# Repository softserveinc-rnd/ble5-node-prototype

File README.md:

# BLE5 node for prototyping

## Hardware Design

The designed system is built around Nordic nRF52840 module that is used as a main
communication and processing unit. 
Nordic Semiconductor’s nRF52840 Bluetooth Low Energy (BLE) System-on-Chip
(SoC) — the high-end variant of Nordic’s nRF52 Series of high-performance
Bluetooth 5-certified SoCs — brings a production-ready, multiprotocol wireless
IoT solution to the market with the full Bluetooth 5 support and support for Bluetooth
mesh and Thread.

The SoC offers the capabilities and flexibility to support a broad range of networked,
connected products for wearables, gaming, VR/AR, as well as home and industrial IoT applications
thanks to a wide range of features and peripherals.

The high-end nRF52840 SoC, based on Nordic’s proven nRF52 Series architecture,
is the first single-chip solution to bring all of the benefits of Bluetooth 5 to the market.
The key advantages of Bluetooth 5 compared to the previous implementations of the BLE specification
include: 2× on-air raw data bandwidth (2 Mb/s); 4× range; 8× broadcasting ability with advertising
extensions that increase the advertising packet payload size to 251 bytes; and an improved channel
coexistence algorithm.

The nRF52840 SoC uses a 64-MHz, 32-bit Arm Cortex M4F processor, floating point, and DSP performance
to meet the demands of challenging wireless applications. The SoC can also operate from the power
supplies above 5 V, such as rechargeable battery power sources.

Other features include a new radio architecture with a +8-dBm on-chip PA, 1-MB flash and 256-kB RAM,
IEEE 802.15.4 (including Thread), ANT, Zigbee, and proprietary 2.4-GHz wireless technologies;
a full-speed USB 2.0 controller; and a host of peripherals including a quad-SPI interface.
In terms of security, the SoC incorporates an Arm CryptoCell-310 cryptographic accelerator.
Extensive crypto-ciphers and key generation and storage options are also available.

There is a set of sensors to measure ambient and usage conditions: 

1. Temperature, humidity for monitoring environment (HTS221).
2. Inertial Measurement Unit(IMU) Accelerometer, gyroscope for monitoring node position, movement and fall detection (LSM6DSM).
3. Pressure sensor for altitude monitoring(LPS22HBTR, also can be used for navigation purposes)  
4. Lighting intensity sensor (OPT3001).

These sensors use I2C bus for communication with Nordic MCU.

The 1.8V LDO is used to power the system from LiPo battery. All the components were selected to run from low voltage level.
There are 2 power switches on the board that are controlled by Nordic chip. These switches are used to power sensors and flash memory.
To minimize power consumption during the sleep mode they can be turned off.

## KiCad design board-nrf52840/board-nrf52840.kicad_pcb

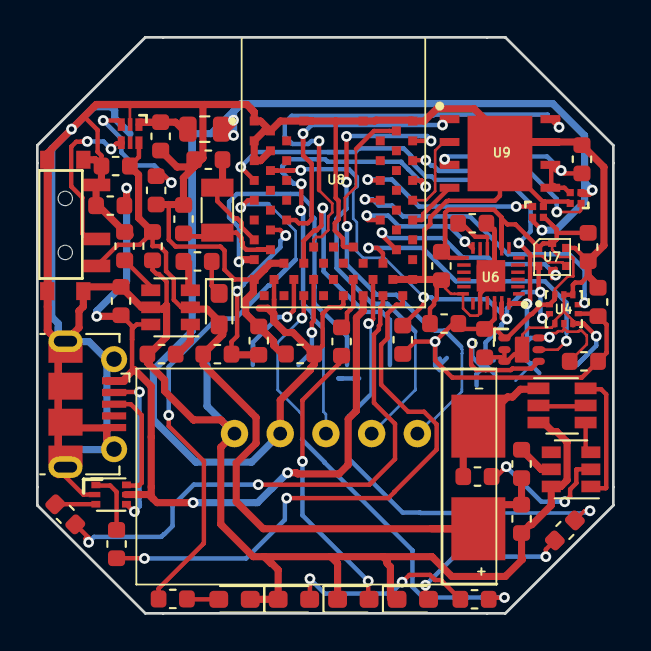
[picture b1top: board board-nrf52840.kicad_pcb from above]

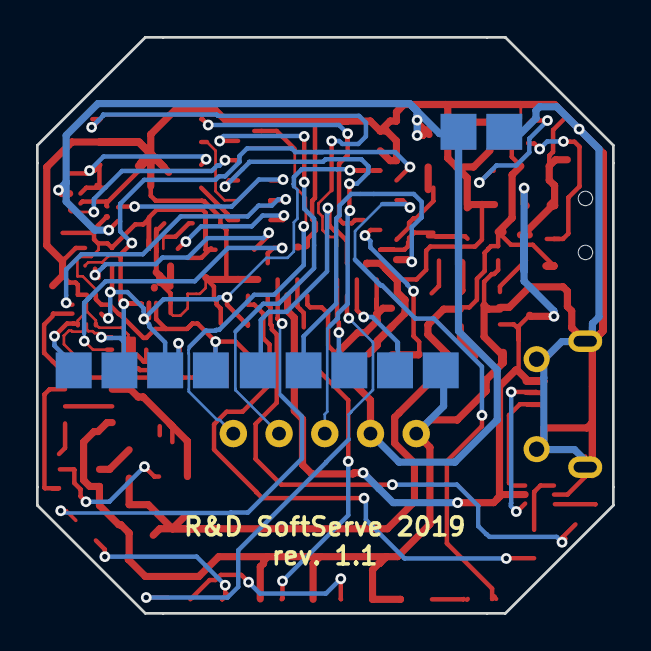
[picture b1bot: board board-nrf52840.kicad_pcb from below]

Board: 2 copper layers, 32.0 x 32.0 mm, 59 parts (4 on the bottom side), 56 nets.

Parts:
BT1: Battery; BATT-xx1220
C1, C3, C6: 1uF; C_0603_1608Metric
C2, C14: 0.1; C_0603_1608Metric
C4: 100nF; C_0603_1608Metric
C5, C9, C10, C11, C12, C17: 0.1uF; C_0603_1608Metric
C7: 4.7; C_0603_1608Metric
C8: 0.01; C_0603_1608Metric
C13: 4.7uF; C_0603_1608Metric
C15, C16: 6pF; C_0603_1608Metric
D1: LED; LED_0603_1608Metric_Pad1.05x0.95mm_HandSolder
D2: LED_RED; LED_0603_1608Metric_Pad1.05x0.95mm_HandSolder
D3: LED_GREEN; LED_0603_1608Metric_Pad1.05x0.95mm_HandSolder
D4: LED_BLUE; LED_0603_1608Metric_Pad1.05x0.95mm_HandSolder
D5: LED_YELLOW; LED_0603_1608Metric_Pad1.05x0.95mm_HandSolder
J1: USB_OTG; USB_Micro-B_Molex-105017-0001
J2: SWD
J3: Alternative_power; external_power
J4: Conn_01x05_Female; Pogo_5_pins
J5: I2C_sensors; 4x_pins
L1: 330 OHM @ 100MHz; L_0805_2012Metric
Q1: SMC8205AS; TSOT-23-6
R1, R4: 10k; R_0603_1608Metric
R2: 1.5k; R_0603_1608Metric
R3: 100R; R_0603_1608Metric
R5: 1k; R_0603_1608Metric
R6: 1M; R_0603_1608Metric
R7: 220k; R_0603_1608Metric
R8, R9: 4.7k; R_0603_1608Metric
R10, R11, R12, R13: 220R; R_0603_1608Metric
R14, R15: 27R; R_0603_1608Metric
SW1: SW_SPDT_GND; PCM12SMTR
U1: bq21040; SOT-23-6
U2: DW01; SOT-23-6
U3: USBLC6-2P6; SOT-666
U4: LPS22HBTR; LGA10R50P2X3_200X200X80
U6: Val**; ICM-20948
U7: HTS221; HLGA-6L
U8: BMD-340-A-R; BMD340AR
U9: AT45DB641E-MHN-Y; SON127P600X500X60-9N-D
U10, U12: SiP32475; μDFN-4L_1_mm_x_1 mm
U11: OPT3001; USON_PACKAGE
U13: LDK120_; DFN6L
Y1: Crystal; Crystal_SMD_3215-2pin_3.2x1.5mm

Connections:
+1V8: C7.1, L1.1, U13.1
Analog_1_P0.03: J4.2, U8.19
Analog_2_P0.05: J4.3, U8.21
Analog_3_P0.02: J4.4, U8.15
Analog_4_P0.04: J4.5, U8.20
DRDY: U7.3, U8.32
FLASH_PWR_EN: U8.41, U12.1
GND: C1.2, C2.2, C3.2, C4.1, C5.1, C6.2, C7.2, C8.2, C9.1, C10.1, C11.1, C12.1, C13.1, C14.2, C15.1, C16.1, C17.1, D2.1, D3.1, D4.1, D5.1, J1.5, J1.6, J2.1, J3.1, J4.1, J5.1, Q1.3, R1.2, R4.2, R7.2, SW1.1, SW1.4, U1.5, U2.6, U3.2, U4.3, U4.5, U4.8, U4.9, U6.9, U6.18, U6.20, U6.25, U7.5, U8.1, U8.2, U8.3, U8.4, U8.5, U8.16, U8.18, U8.29, U8.30, U8.45, U8.46, U8.47, U8.55, U9.7, U9.9, U10.4, U11.2, U11.3, U12.4, U13.2
I2C_SCL: J5.3, R8.1, U4.2, U6.23, U7.2, U8.6, U11.4
I2C_SDA: J5.2, R9.1, U4.4, U6.24, U7.4, U8.7, U11.6
INT1_IMU: U6.12, U8.56
INT_DTR: U4.7, U8.57
INT_OPT3004: U8.28, U11.5
unnamed: BT1.2, Q1.1, R5.2
unnamed: C8.1, U13.3
unnamed: C12.2, U6.10
unnamed: D1.1, R2.1
unnamed: D2.2, R10.1
unnamed: D3.2, R11.1
unnamed: D4.2, R12.1
unnamed: D5.2, R13.1
unnamed: J1.2, U3.4
unnamed: J1.3, U3.6
unnamed: Q1.2, Q1.5
unnamed: Q1.4, U2.3
unnamed: Q1.6, U2.1
unnamed: R1.1, U1.1
unnamed: R2.2, U1.3
unnamed: R3.1, U2.5
unnamed: R4.1, U1.4
unnamed: R5.1, U2.2
unnamed: R14.2, U8.67
unnamed: R15.2, U8.68
unnamed: SW1.2, U13.4
P0.09: R13.2, U8.25
P0.11: R12.2, U8.27
P0_0: C15.2, U8.13, Y1.1
P0_1: C16.2, U8.14, Y1.2
P0_28: R10.2, U8.9
P1_14: R11.2, U8.63
RESET: J2.3, U8.39
SENS_PWR_EN: U8.58, U10.1
SPI_MISO: U8.53, U9.8
SPI_MOSI: U8.52, U9.1
SPI_NSS: U8.35, U9.4
SPI_SCK: U8.37, U9.2
SWDCLK: J2.4, U8.43
SWDIO: J2.5, U8.44
USB_N: R14.1, U3.3
USB_P: R15.1, U3.1
VBUS: C1.1, C2.1, J1.1, U1.6, U3.5, U8.66
VCC: C13.2, J2.2, J3.2, L1.2, U8.17, U8.65, U10.2, U12.2
VCCQ: C5.2, C9.2, C10.2, C11.2, C17.2, J5.4, R8.2, R9.2, U4.1, U4.6, U4.10, U6.8, U6.13, U6.22, U7.1, U7.6, U10.3, U11.1
VDDF: C14.1, U9.3, U9.5, U9.6, U12.3
V_BAT: BT1.1, C3.1, C4.2, C6.1, D1.2, R3.2, R6.1, SW1.3, U1.2, U13.6
V_BAT_LEV: R6.2, R7.1, U8.12

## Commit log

2019-05-27 Initial description
2019-05-27 Fixed description: headers and image link
2019-05-30 Updated - corrected typos.
2019-05-30 Added board schematic and pcb
2019-05-30 Fixed 3d models and footptints
2019-05-30 Updated README.md - Added 3d view
2019-05-30 Updated README.md - Fixed 3d view width
2019-05-30 Updated README.md - Fixed 3d view image
2019-05-30 Fixed Crystal 3D model
